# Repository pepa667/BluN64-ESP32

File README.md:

# Project archived in favor of BluControl

This project was archived in favor of [BluControl](https://github.com/JPZV/BluControl-ESP32/), which is config based and compatible with many types of controls.

---

# BluN64-ESP32

This is a project to emulate a N64 controller as a modern one with ESP32. It works with (almost) any ESP32 and with any original N64 controller (from the original console, not the Switch one).

It's also compatible with the original joystick, so there is no need of using an alternative one or doing your own with analogs.

## Installation

The recommended way is to go to the [Online Installer](https://jpzv.github.io/BluN64-ESP32/) from a supported browser (like Chrome), connect your ESP32 in Boot/Flash mode, and click in Install. It'll always install the latest version.

The other way is to clone the project and building it yourself, thought this is **not recommended** for new users.

## Pinout and schematics

In the [Hardware](/hardware) directory, you can find some useful files for building your own controller. Sadly there is no tutorial about building steps by step except for a [Step-By-Step draft in spanish](/hardware/Assembly%20steps%20-%20ES.txt), but I added all the photos that I took while doing my own controller, so I hope it helps you.

You can find also the Pinout for both the [ESP32](/hardware/ESP32%20Pinout.png) and the [Gamepad itself](/hardware/GamePad%20Pinout.png). You zoom them a lot so do it if you cannot read something.

Please note, you **have** to join the **JP5** mounting point (at the right of the controller). And, if your controller has a capacitor named **C10** above the joystick's connector, **don't** remove it. The rest of the components (resistors, IC, capacitors, jumpers, etc.) **must** be removed before connecting your ESP32.

Also, if you speak Spanish, you can follow [MundoYakara's video](https://youtu.be/PrA_Gp_z_Fw) where he builds a N64 controller with this project. Just keep in mind that he uses **another pinout which is NOT compatible with the binaries from this repository**. This means that you'll need to flash with his binaries which may not be up to date. Another workaround would be to use his video as a walkthrough but using the pinout from this repository.

## Using it

After flashing it for the first time, the BluN64 will start in *Switch Mode*, this means that the control will try to connect to an already paired Nintendo Switch, or to a Nintendo Switch in pair mode (i.e. in "**Change Grip/Order**"). If you want to change to *BlueRetro Mode*, you have to press **L, R and Start at the same time** for about five seconds until the Mode LED (**GPIO 16**) turns off. In *BlueRetro Mode*, the controller will be available for every type of device, including any console with a [BlueRetro](https://github.com/darthcloud/BlueRetro) on it, Android Device, Windows, etc. It'll work as a generic controller so everything should be working without any problem. To go back to *Switch Mode*, you have to do the same steps (**L + R + Start** for **5 seconds**)

You can switch between both modes on-the-fly, you don't have to shut down neither the controller nor the console for switching, and every time you turn on the controller it'll start on the latest mode used.

In Nintendo Switch, to press the *Home Button* without a physical button wired to **GPIO 2**, you can press both **Start** and then **L** at the same time. The same thing applies to *ZR* (which can be optionally wired to **GPIO 4**), but this time with **Start** and **R**

## Cloning and building

I'd recommend you to clone this repository using the GitHub Desktop app, otherwise, always remember to add `--recursive` to your `git clone` command. **Don't download this project as a ZIP**

For building, I recommend you to build it using Visual Studio Code with the [Espressif IDF](https://marketplace.visualstudio.com/items?itemName=espressif.esp-idf-extension) extension and with ESP-IDF 5.0 or newer installed. Remember to open the project as a Workplace by going to `File -> Open Workspace from File -> ./.vscode/BluN64-ESP32.code-workspace` on Visual Studio Code. You have to build both the n64-switch and n64-blueretro projects, one at the time, then, you have to flash them manually to your ESP32 using **ESP Flash Tool** with the following parameters

```
n64-switch/build/bootloader/bootloader.bin @ 0x1000
n64-switch/build/partition-table/partition-table.bin @ 0x8000
n64-switch/build/ota_data_initial.bin @ 0xd000
n64-switch/build/n64-control-switch.bin @ 0x10000
n64-blueretro/build/n64-control-blueretro.bin @ 0x110000
```

## Contributing

Pull requests are welcome. For major changes, please open an issue first to discuss what you would like to change.

## Special thanks

[dpedu.io](https://dpedu.io/article/2015-03-11/nintendo-64-joystick-pinout-arduino) for his blog about N64 analogs with Arduino

[Jacques Gagnon (AKA Darthcloud)](https://github.com/darthcloud) for his help with [BlueRetro](https://github.com/darthcloud/BlueRetro/) ([License](https://github.com/darthcloud/BlueRetro/blob/master/LICENSE))

[Mitch Cairns (From Hand Held Legend)](https://github.com/mitchellcairns) for his help with [HOJA](https://github.com/HandHeldLegend/HOJA-LIB-ESP32) ([License](https://github.com/HandHeldLegend/HOJA-LIB-ESP32/blob/main/LICENSE.md))

[Yakara Colombia](https://github.com/yakaracolombia) for his support, contributions and ideas

## License

This project uses [Creative Commons BY-NC-SA 4.0 license](/LICENSE). This means that you can modify and distribute it in a non-commercial way, but you **must** credit the original project and under the same license. You can read more about that in [Create Commons website](https://creativecommons.org/licenses/by-nc-sa/4.0/)

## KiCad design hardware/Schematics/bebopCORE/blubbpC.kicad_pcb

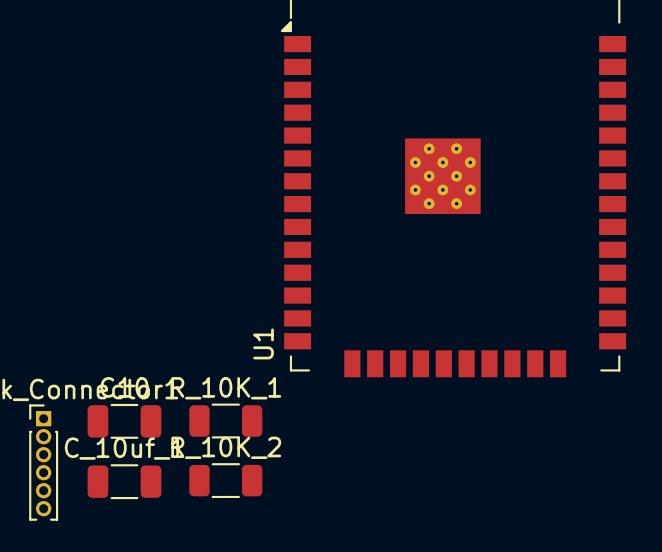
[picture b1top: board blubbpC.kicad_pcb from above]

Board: 2 copper layers, 6 parts (0 on the bottom side), 8 nets, no tracks yet.

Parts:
C10: C_Small; C_1206_3216Metric
C_10uf_1: C_Small; C_1206_3216Metric
Joystick_Connector1: Conn_01x06_Male; PinHeader_1x06_P1.00mm_Vertical
R_10K_1, R_10K_2: R_Small; R_1206_3216Metric
U1: ESP32-WROOM-32D; ESP32-WROOM-32

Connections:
+3.3V: C10.1, Joystick_Connector1.2, R_10K_1.1, U1.2 (VDD)
/Joystick_X1: Joystick_Connector1.1, U1.6 (IO34)
/Joystick_X2: Joystick_Connector1.4, U1.7 (IO35)
/Joystick_Y1: Joystick_Connector1.5, U1.8 (IO32)
/Joystick_Y2: Joystick_Connector1.6, U1.9 (IO33)
GND: C10.2, C_10uf_1.2, Joystick_Connector1.3, U1.1 (GND), U1.15 (GND), U1.38 (GND), U1.39 (GND)
unnamed: C_10uf_1.1, R_10K_1.2, U1.3 (EN)
unnamed: R_10K_2.1, U1.27 (IO16)

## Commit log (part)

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2026-04-11 Clean Reset
2026-04-11 Update submodule
2026-04-11 First Build
2026-04-11 Firmware
2026-04-12 Adicionado script shell para agilizar o commit dos submodules
2026-04-16 TEstes e mais testes
2026-04-17 1st Build
2026-04-17 Rebrand
2026-04-17 Atualizar o .gitmodules
2026-04-17 Quick fixes
2026-04-17 UPDATE.md — log
2026-04-18 tudinovo
2026-04-23 Update GPIO pin assignments for N64 controller
2026-04-23 Update BUTTONS_BIT_MASK to include BUTTON_SELECT_PIN
2026-04-23 Comment out unused button mappings in main.c
    Comment out unused button mappings and combinations for clarity.
2026-04-23 Update GitHub Actions workflow for BebopCORE-ESP32
2026-04-23 Change repository clone URL in build workflow
2026-04-23 Update upload-artifact action to version 4
2026-04-23 Add Python 3.10 setup step to build workflow
    Added step to set up Python 3.10 in the build workflow.
2026-04-23 Update build.yml to install prerequisites and set python3
    Added steps to set python3 as default and install prerequisites.
2026-04-24 Change Python version and add workflow_dispatch
    Updated Python version from 3.10 to 3.8 and added workflow_dispatch trigger.
2026-04-24 Disable joystick input handling temporarily
    Commented out joystick input handling code.
2026-04-24 Update GPIO definitions for N64 controller
2026-04-24 Disable joystick definitions and functions
    Comment out joystick-related definitions and functions.
2026-04-24 Comment out joystick handling code
    Comment out joystick value variables and related functions.
2026-04-24 Disable joystick input handling and change subcore
    Comment out joystick handling and adjust core type
2026-04-24 Disable C-buttons, Z-trigger, and joystick inputs
2026-04-24 Fix: Remove undefined pin references from n64-blueretro/main/main.cpp
    - Removed reference to TRIGGER_Z_PIN (not defined in pinout)
    - Removed C-buttons handling (C_UP_PIN, C_DOWN_PIN, C_LEFT_PIN, C_RIGHT_PIN not defined)
    - Removed joystick axis handling (functions not defined)
    - Removed unused variables (x_axis, y_axis, prev_x_axis, etc.)
    - Restored buttonsLength from 6 to 5 (matching available pins)
    - Aligns with n64-switch implementation for Nintendo Switch mode
2026-04-24 Add nvs_flash_init before Bluetooth/HOJA initialization
    Agent-Logs-Url: https://github.com/pepa667/BebopCORE-ESP32/sessions/9c4d3de9-1aa5-428f-8c41-bda21d356be0
2026-04-24 fix: Add NVS flash include required for ESP-IDF bluetooth initialization
2026-04-24 Remove all joystick-related code and comments from n64-pad.c (no joystick in hardware).
2026-04-24 Remove all joystick-related definitions and code. Document joystick is not present in hardware.
2026-04-24 Remove all joystick code references and dead comments. Document absence of joystick on this hardware.
2026-04-24 Cleaning
2026-04-24 teste
2026-04-24 self hosted build
2026-04-24 BUILDING FIRMWARE
2026-04-24 Build CI workflow
2026-04-24 Archive project and link to BluControl
    Updated README to indicate project archiving in favor of BluControl.
2026-04-24 Trying to fix firmware boot
2026-04-25 Fix: Corrigir erros de compilação no main.c - campos da struct renomeados
2026-04-25 Initial plan
2026-04-25 Add ble-notify-wrapper component to fix ble_gatts_notify_custom build error
    Agent-Logs-Url: https://github.com/pepa667/BebopCORE-ESP32/sessions/03434044-3659-4a9f-90b9-49179332d2d9
2026-04-25 fix: update esp-nimble-cpp submodule to include ble_notify_wrapper.h for ESP-IDF v5+
2026-04-25 Tentando fazer commit...
2026-04-25 Update esp-nimble-cpp submodule to use branch release/2.0
    Agent-Logs-Url: https://github.com/pepa667/BebopCORE-ESP32/sessions/ee35723a-c379-4cdf-959d-1eb9ce739392
2026-04-25 Now building locally, please wait...
2026-04-25 restore
2026-04-25 Testing
2026-04-25 Removed submodule <name>
2026-04-25 Modify button length and clean up joystick code
    Updated button configuration and commented out unused joystick code.
2026-04-25 Fresh Start
2026-04-25 First test, again
2026-04-25 Funciona PORR@@@@@!!!!
